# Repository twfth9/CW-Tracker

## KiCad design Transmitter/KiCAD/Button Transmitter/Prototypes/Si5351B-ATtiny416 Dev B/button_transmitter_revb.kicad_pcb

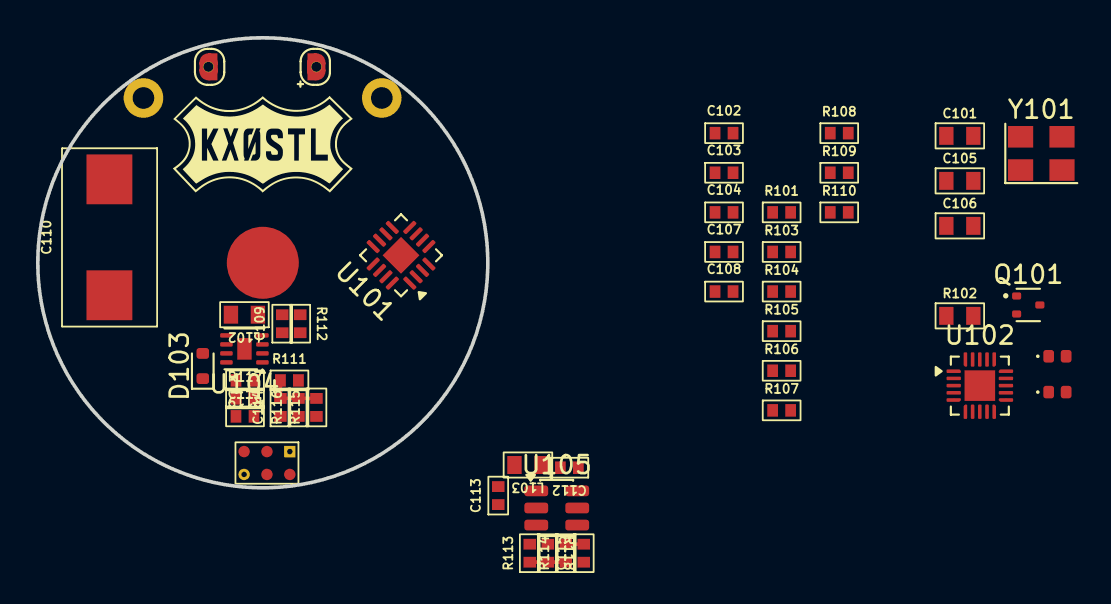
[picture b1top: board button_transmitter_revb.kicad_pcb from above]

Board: 4 copper layers, 25.0 x 25.0 mm, 52 parts (1 on the bottom side), 33 nets.

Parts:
BT101: CR2032; BatteryHolder_Keystone_3034_1x20mm
BZ101: 7BB-20-3; Buzzer_Pad_POS
BZ102: 7BB-20-3; Buzzer_Pad_NEG
C101: 10uF; Worthington_C_0603
C102, C103, C104, C108, C111, C112, C113, C114: 100nF; Worthington_C_0402
C105, C106: 22uF; Worthington_C_0603
C107, C109: 1uF; Worthington_C_0402
C110: 47uF; Worthington_CTant_2917
C115: 220pF; Worthington_C_0402
D101: RED; Worthington_LED_0402_1005Metric
D102: GREEN; Worthington_LED_0402_1005Metric
D103: D_Schottky; D_SOD-523
J101: 1.27mm Pogo Pads For Programming & Debug; 2x3_1.27mm_Pogo_Header
J102: Antenna Spring; RF_Solder_Pad
L101: 100mH; L_Axial_L12.0mm_D5.0mm_P15.24mm_Horizontal_Fastron_MISC
L102: 10uH; Worthington_L_0603
L103: 4u7H; Worthington_L_0603
Q101: DMN601TK-7; SOT-523
R101: 15k; Worthington_R_0402
R102: 15k; Worthington_R_0603
R103: 600; Worthington_R_0402
R104: 0R; Worthington_R_0402
R105, R114, R115: 1k; Worthington_R_0402
R106, R109: 1M; Worthington_R_0402
R107, R108: 10; Worthington_R_0402
R110: 500; Worthington_R_0402
R111: 3M; Worthington_R_0402
R112: 2k2; Worthington_R_0402
R113: 402k; Worthington_R_0402
R116: 200k; Worthington_R_0402
R117: 107k; Worthington_R_0402
R118: 127k; Worthington_R_0402
R119: 5k; Worthington_R_0402
U101: Si5351B-B-GM1; QFN-16-1EP_3x3mm_P0.5mm_EP1.45x1.45mm
U102: ATtiny416-M; VQFN-20-1EP_3x3mm_P0.4mm_EP1.7x1.7mm
U103: Case; Case_CR2032
U104: MIC2288YML; WDFN-8-1EP_2x2mm_P0.5mm_EP0.8x1.2mm
U105: TPP361081; TSOT-23-6
Y101: 25MHz; Crystal_SMD_Kyocera_CX3225SB-4Pin_3.2x2.5mm

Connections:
+2V5: C101.1, C102.1, C103.1, C113.2, D101.2 (A), J101.2, L101.2, L103.2, R101.2, R102.2, R113.2, U101.9 (VDDOA), U101.16 (VDD)
+BATT: C104.1, C105.1, C106.1, U102.4 (VCC)
/2V5_RAIL_EN: U102.5 (PA4), U105.5 (EN)
/BOOST_EN: U102.10 (PB4), U104.3 (EN)
/BUZZER_PULSE: D102.2 (A), R108.1, U102.15 (PC0)
/CHARGE_AIN7: R115.1, U102.8 (PA7)
/CLK3: J102.1 (In), R104.2
/CLK3_T: R104.1, U101.12 (CLK3)
/MCU_DAC0: J101.5, R105.1, U102.7 (PA6)
/MCU_SCL: J101.4, R102.1, U101.4 (SCL), U102.1 (PA2)
/MCU_SDA: J101.3, R101.1, U101.5 (SDA), U102.20 (PA1)
/MCU_UPDI: J101.1, U102.19 (~RESET/PA0)
/~TX_EN: U101.6 (OEB), U102.12 (PB2)
GND: BT101.2, BZ102.2 (-), C101.2, C102.2, C103.2, C104.2, C105.2, C106.2, C108.1, C109.1, C110.2, C111.1, C113.1, C114.1, C115.1, J101.6, Q101.2 (S), R103.2, R106.2, R109.2, R110.2, R116.1, R118.1, R119.1, U101.15 (GND), U101.17 (GND), U102.3 (GND), U102.21 (GND), U104.4 (AGND), U104.8 (PGND), U104.9 (PAD), U105.1 (GND), Y101.2, Y101.4
unnamed: BT101.1 (+), R112.2
unnamed: BZ101.1 (+), C107.2, R106.1
unnamed: C107.1, L101.1, R107.2
unnamed: C114.2, R111.1, R115.2, R116.2
unnamed: D101.1 (K), R103.1
unnamed: D102.1 (K), R110.1
unnamed: D103.2 (A), L102.2, U104.7 (SW)
unnamed: C110.1, C111.2, D103.1 (K), R111.2, R117.2, U104.1 (OVP), U105.3 (VIN)
unnamed: Q101.3 (D), R107.1
unnamed: Q101.1 (G), R108.2, R109.1
unnamed: R113.1, R114.1, R118.2
unnamed: C108.2, R105.2, U101.3 (VC)
unnamed: U101.1 (XA), Y101.3
unnamed: U101.2 (XB), Y101.1
unnamed: R117.1, R119.2, U104.6 (FB)
unnamed: C109.2, L102.1, R112.1, U104.2 (VIN)
unnamed: C112.2, L103.1, U105.2 (SW)
unnamed: C112.1, U105.6 (VBST)
unnamed: C115.2, R114.2, U105.4 (VFB)

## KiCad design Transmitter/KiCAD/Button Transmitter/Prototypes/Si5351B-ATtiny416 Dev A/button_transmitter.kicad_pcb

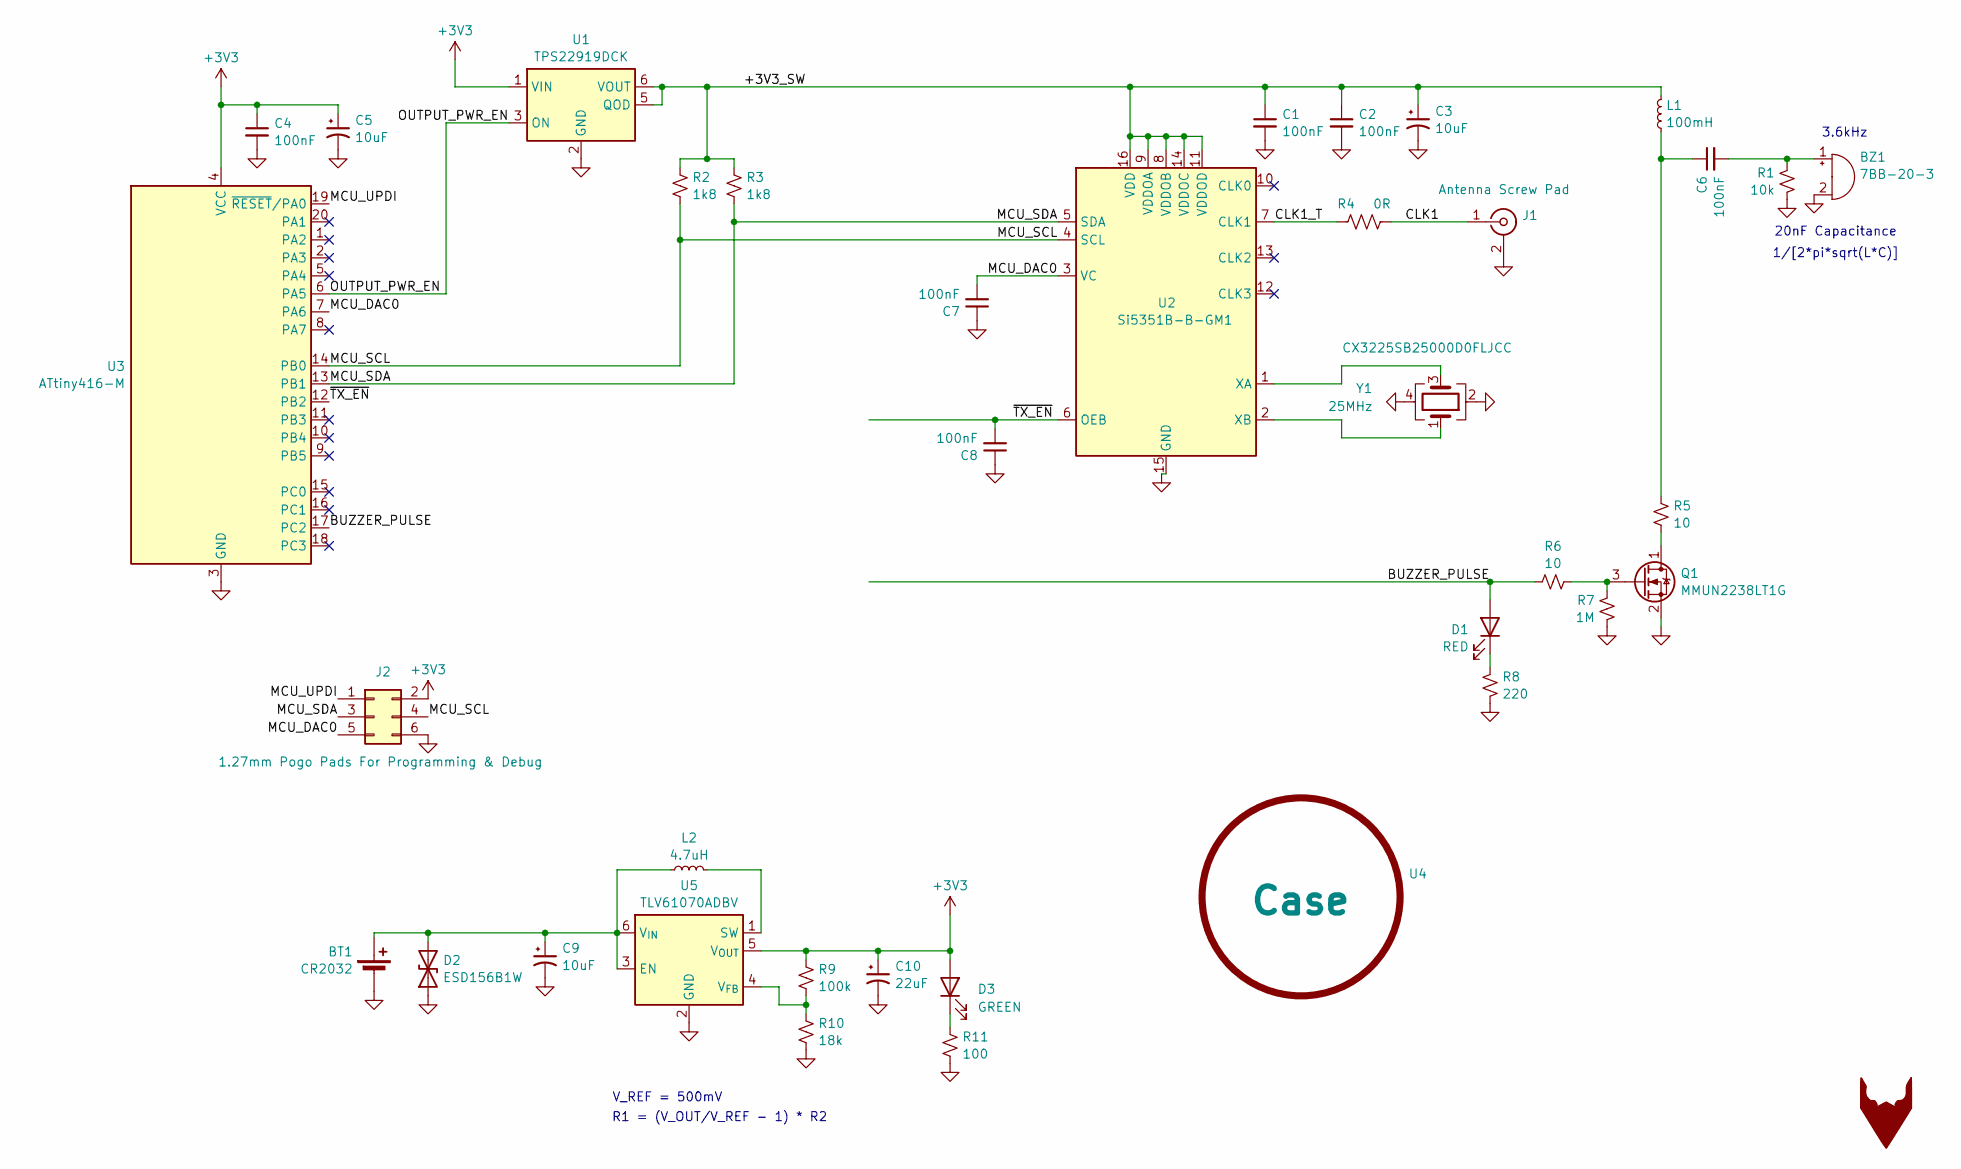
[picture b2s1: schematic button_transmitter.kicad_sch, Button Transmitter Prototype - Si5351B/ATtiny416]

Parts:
BT1: CR2032; BatteryHolder_Keystone_3034_1x20mm_CUTOUT
BZ1: 7BB-20-3; Buzzer_Pad_POS
BZ2-1: 7BB-20-3; Buzzer_Pad_NEG
C1, C2, C4, C6, C7, C8: 100nF; Worthington_C_0402_1005Metric
C3, C5, C9: 10uF; Worthington_C_0402_1005Metric
C10: 22uF; C_0603_1608Metric
D1: RED; Worthington_LED_0402_1005Metric
D2: ESD156B1W; D_0201_0603Metric
D3: GREEN; Worthington_LED_0402_1005Metric
J1: Antenna Screw Pad; RF_Solder_Pad
J2: 1.27mm Pogo Pads For Programming & Debug; 2x3_1.27mm_Pogo_Header
L1: 100mH; L_Axial_L12.0mm_D5.0mm_P15.24mm_Horizontal_Fastron_MISC
L2: 4.7uH; L_0805_2012Metric
Q1: MMUN2238LT1G; SOT-23-3
R1: 10k; Worthington_R_0402_1005Metric
R2: 1k8; R_0402_1005Metric
R3: 1k8; R_0603_1608Metric
R4: 0R; Worthington_R_0402_1005Metric
R5, R6: 10; Worthington_R_0402_1005Metric
R7: 1M; Worthington_R_0402_1005Metric
R8: 220; Worthington_R_0402_1005Metric
R9: 100k; Worthington_R_0402_1005Metric
R10: 18k; Worthington_R_0402_1005Metric
R11: 100; Worthington_R_0402_1005Metric
U1: TPS22919DCK; SOT-363_SC-70-6
U2: Si5351B-B-GM1; QFN-16-1EP_3x3mm_P0.5mm_EP1.45x1.45mm
U3: ATtiny416-M; VQFN-20-1EP_3x3mm_P0.4mm_EP1.7x1.7mm
U4: Case; Case_CR2032
U5: TLV61070ADBV; SOT-23-6
Y1: 25MHz; Crystal_SMD_Kyocera_CX3225SB-4Pin_3.2x2.5mm

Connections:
+3V3: C4.1, C5.1, C10.1, D3.2 (A), J2.2, R9.1, U1.1 (VIN), U3.4 (VCC), U5.5 (V_{OUT})
/+3V3_SW: C1.1, C2.1, C3.1, L1.2, R2.1, R3.1, U1.5 (QOD), U1.6 (VOUT), U2.8 (VDDOB), U2.9 (VDDOA), U2.11 (VDDOD), U2.14 (VDDOC), U2.16 (VDD)
/BUZZER_PULSE: D1.2 (A), R6.1, U3.17 (PC2)
/CLK1: J1.1 (In), R4.2
/CLK1_T: R4.1, U2.7 (CLK1)
/MCU_DAC0: C7.2, J2.5, U2.3 (VC), U3.7 (PA6)
/MCU_SCL: J2.4, R2.2, U2.4 (SCL), U3.14 (PB0)
/MCU_SDA: J2.3, R3.2, U2.5 (SDA), U3.13 (PB1)
/MCU_UPDI: J2.1, U3.19 (~RESET/PA0)
/OUTPUT_PWR_EN: U1.3 (ON), U3.6 (PA5)
/~TX_EN: C8.2, U2.6 (OEB), U3.12 (PB2)
GND: BT1.2, BZ2-1.2 (-), C1.2, C2.2, C3.2, C4.2, C5.2, C7.1, C8.1, C9.2, C10.2, D2.1 (A1), J1.2 (Ext), J2.6, Q1.2 (S), R1.2, R7.2, R8.2, R10.2, R11.2, U1.2 (GND), U2.15 (GND), U2.17 (GND), U3.3 (GND), U3.21 (GND), U5.2 (GND), Y1.2, Y1.4
unnamed: BT1.1 (+), C9.1, D2.2 (A2), L2.1, U5.3 (EN), U5.6 (V_{IN})
unnamed: BZ1.1 (+), C6.2, R1.1
unnamed: C6.1, L1.1, R5.2
unnamed: D1.1 (K), R8.1
unnamed: D3.1 (K), R11.1
unnamed: Q1.1 (D), R5.1
unnamed: Q1.3 (G), R6.2, R7.1
unnamed: U2.1 (XA), Y1.3
unnamed: U2.2 (XB), Y1.1
unnamed: L2.2, U5.1 (SW)
unnamed: R9.2, R10.1, U5.4 (V_{FB})

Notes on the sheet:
20nF Capacitance
3.6kHz
1/[2*pi*sqrt(L*C)]
V_REF = 500mV
R1 = (V_OUT/V_REF - 1) * R2

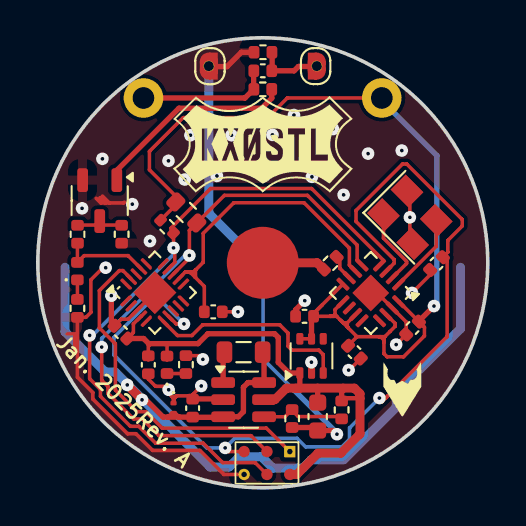
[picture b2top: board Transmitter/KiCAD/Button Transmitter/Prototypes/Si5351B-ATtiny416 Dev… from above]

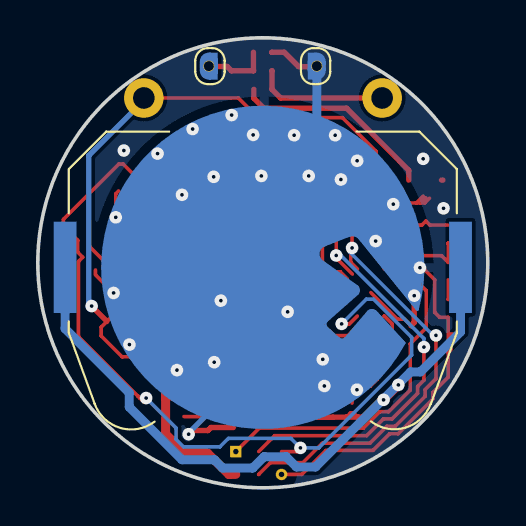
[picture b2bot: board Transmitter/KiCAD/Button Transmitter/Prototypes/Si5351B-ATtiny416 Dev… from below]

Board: 2 copper layers, 25.0 x 25.0 mm, 38 parts (3 on the bottom side), 23 nets.

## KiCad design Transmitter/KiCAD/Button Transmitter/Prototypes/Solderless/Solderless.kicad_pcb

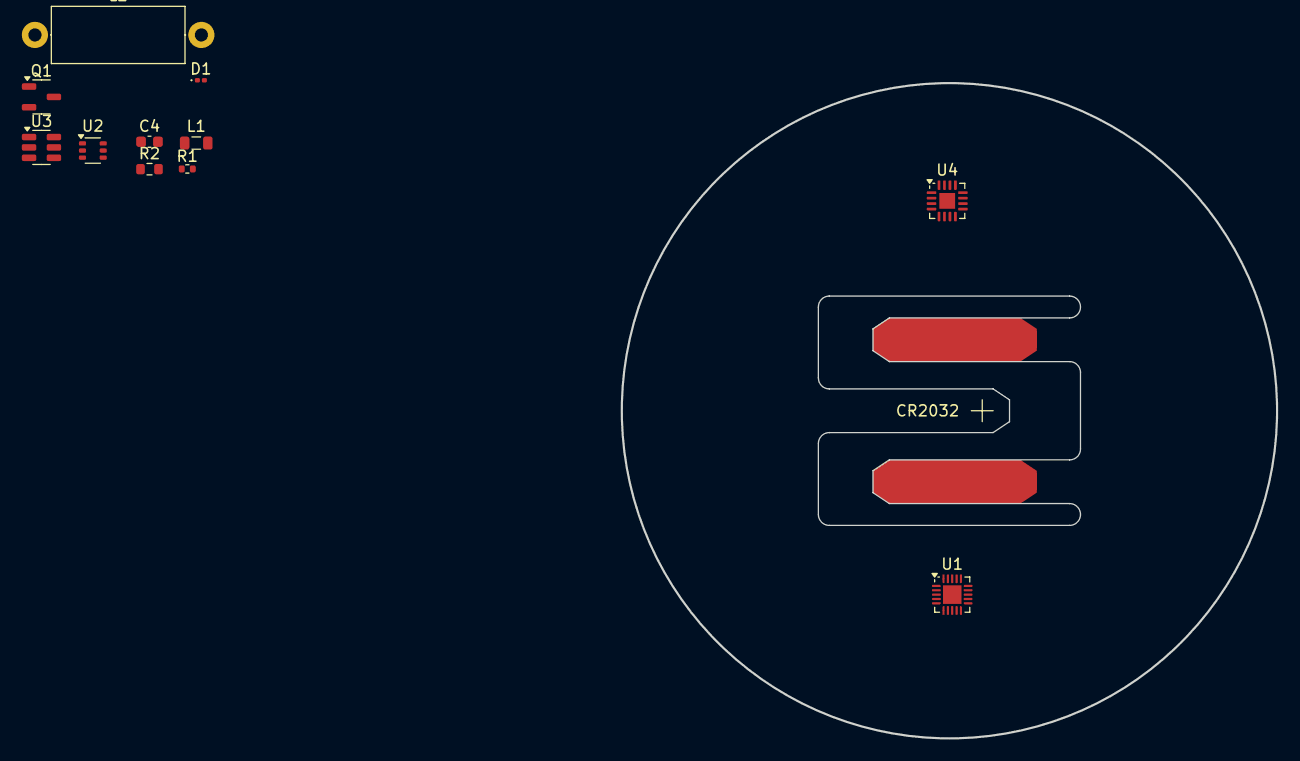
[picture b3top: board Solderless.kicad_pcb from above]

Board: 2 copper layers, 60.0 x 60.0 mm, 12 parts (0 on the bottom side), 10 nets, no tracks yet.

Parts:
BT1: Battery_Cell; CR2032_PCBcutout
C4: 22uF; C_0603_1608Metric
D1: ESD156B1W; D_0201_0603Metric
L1: 4.7uH; L_0805_2012Metric
L2: 100mH; L_Axial_L12.0mm_D5.0mm_P15.24mm_Horizontal_Fastron_MISC
Q1: MMUN2238LT1G; SOT-23-3
R1: 1k8; R_0402_1005Metric
R2: 1k8; R_0603_1608Metric
U1: ATtiny416-M; VQFN-20-1EP_3x3mm_P0.4mm_EP1.7x1.7mm
U2: TPS22919DCK; SOT-363_SC-70-6
U3: TLV61070ADBV; SOT-23-6
U4: Si5351B-B-GM1; QFN-16-1EP_3x3mm_P0.5mm_EP1.45x1.45mm

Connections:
+3V3: C4.1, U1.4 (VCC), U2.1 (VIN), U3.5 (V_{OUT})
/+3V3_SW: L2.2, R1.1, R2.1, U2.5 (QOD), U2.6 (VOUT), U4.8 (VDDOB), U4.9 (VDDOA), U4.11 (VDDOD), U4.14 (VDDOC), U4.16 (VDD)
/MCU_DAC0: U1.7 (PA6), U4.3 (VC)
/MCU_SCL: R1.2, U1.14 (PB0), U4.4 (SCL)
/MCU_SDA: R2.2, U1.13 (PB1), U4.5 (SDA)
/OUTPUT_PWR_EN: U1.6 (PA5), U2.3 (ON)
/~TX_EN: U1.12 (PB2), U4.6 (OEB)
GND: C4.2, D1.1 (A1), Q1.2 (S), U1.3 (GND), U1.21 (GND), U2.2 (GND), U3.2 (GND), U4.15 (GND), U4.17 (GND)
unnamed: D1.2 (A2), L1.1, U3.3 (EN), U3.6 (V_{IN})
unnamed: L1.2, U3.1 (SW)

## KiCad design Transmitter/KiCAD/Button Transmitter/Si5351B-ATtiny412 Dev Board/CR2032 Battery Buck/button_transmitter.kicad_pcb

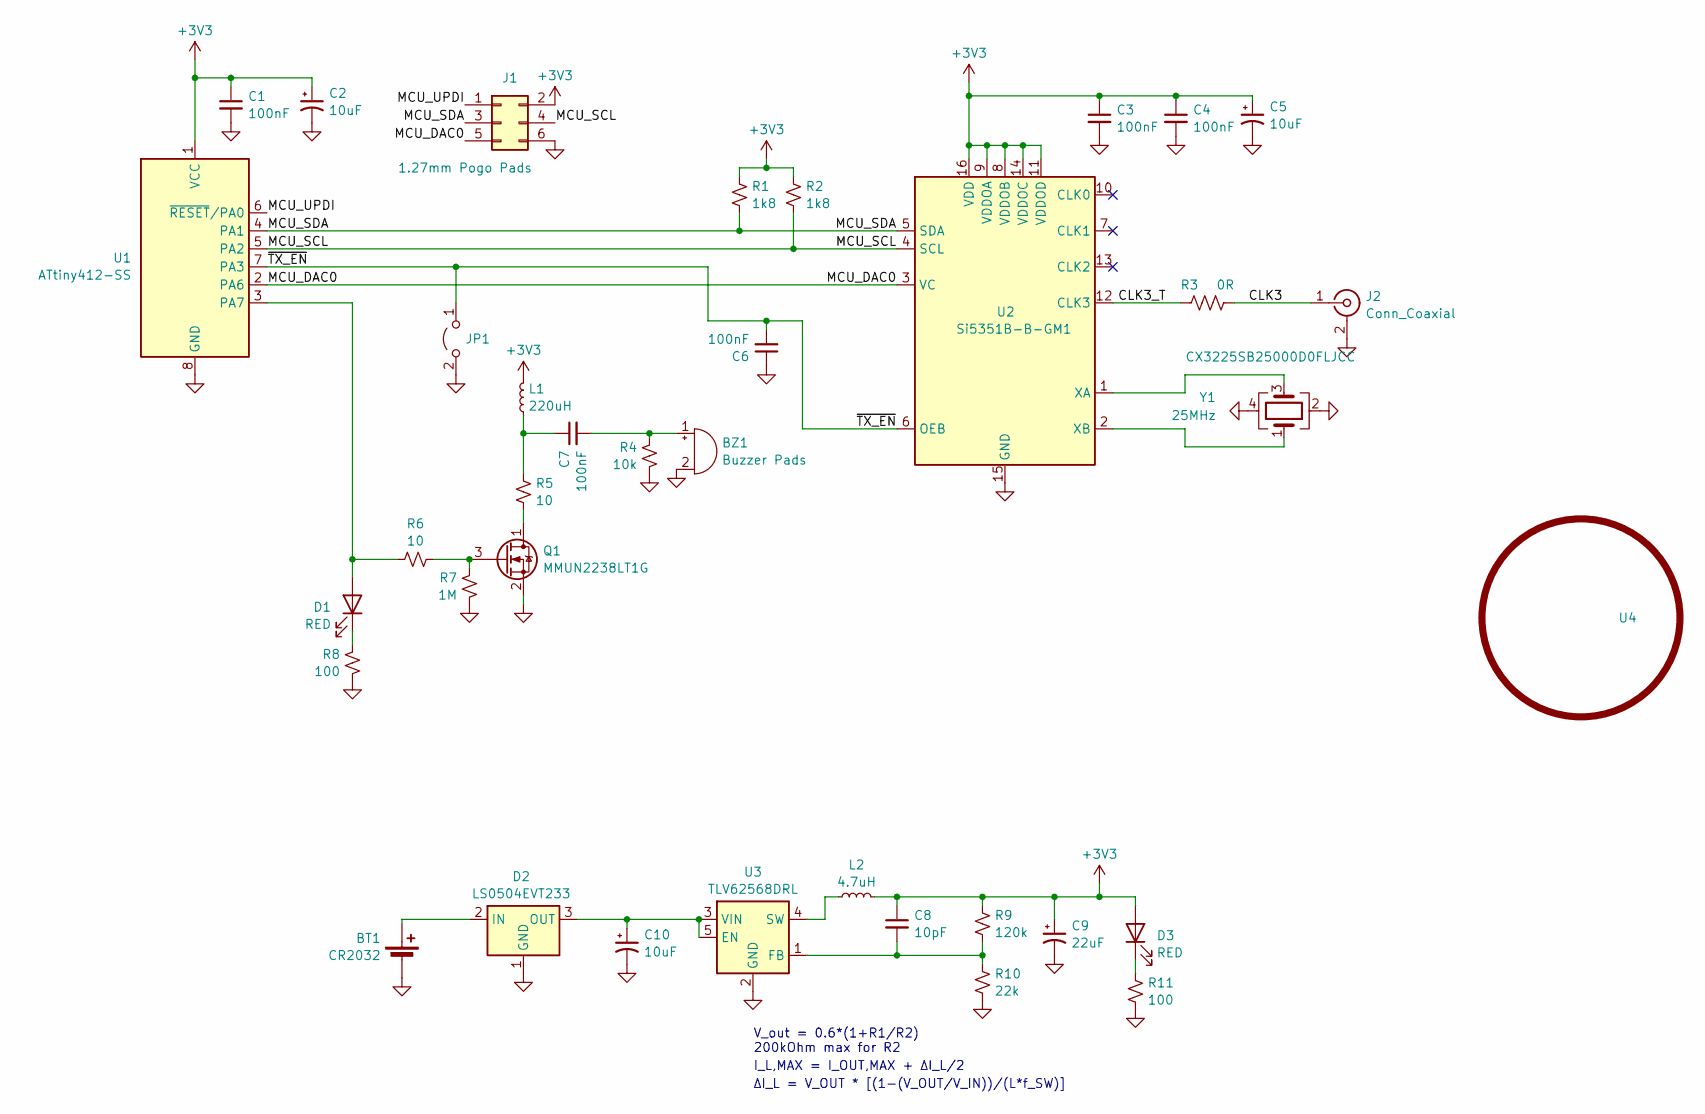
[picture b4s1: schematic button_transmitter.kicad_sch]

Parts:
BT1: CR2032; BatteryHolder_Keystone_3034_1x20mm
BZ1: Buzzer Pads; SolderJumper-2_P1.3mm_Open_RoundedPad1.0x1.5mm
C1, C3, C4, C6, C7: 100nF; R_0402_1005Metric
C2, C5, C10: 10uF; R_0402_1005Metric
C8: 10pF; R_0402_1005Metric
C9: 22uF; R_0603_1608Metric
D1, D3: RED; LED_0402_1005Metric
D2: LS0504EVT233; SOT-23-3
J1: 1.27mm Pogo Pads; 2x3_1.27mm_Pogo_Header
J2: Conn_Coaxial; RF_Solder_Pad
JP1: Jumper_2_Open; SolderJumper-2_P1.3mm_Open_TrianglePad1.0x1.5mm
L1: 220uH; L_1008_2520Metric
L2: 4.7uH; L_0805_2012Metric
Q1: MMUN2238LT1G; SOT-23-3
R1, R2: 1k8; R_0402_1005Metric
R3: 0R; R_0402_1005Metric
R4: 10k; R_0402_1005Metric
R5, R6: 10; R_0402_1005Metric
R7: 1M; R_0402_1005Metric
R8, R11: 100; R_0402_1005Metric
R9: 120k; R_0402_1005Metric
R10: 22k; R_0402_1005Metric
U1: ATtiny412-SS; SOIC-8_3.9x4.9mm_P1.27mm
U2: Si5351B-B-GM1; QFN-16-1EP_3x3mm_P0.5mm_EP1.45x1.45mm
U3: TLV62568DRL; SOT-563
U4: Case_CR2032
Y1: 25MHz; Crystal_SMD_Kyocera_CX3225SB-4Pin_3.2x2.5mm

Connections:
+3V3: C1.1, C2.1, C3.1, C4.1, C5.1, C8.1, C9.1, D3.2 (A), J1.2, L1.2, L2.2, R1.1, R2.1, R9.1, U1.1 (VCC), U2.8 (VDDOB), U2.9 (VDDOA), U2.11 (VDDOD), U2.14 (VDDOC), U2.16 (VDD)
/CLK3: J2.1 (In), R3.2
/CLK3_T: R3.1, U2.12 (CLK3)
/MCU_DAC0: J1.5, U1.2 (PA6), U2.3 (VC)
/MCU_SCL: J1.4, R2.2, U1.5 (PA2), U2.4 (SCL)
/MCU_SDA: J1.3, R1.2, U1.4 (PA1), U2.5 (SDA)
/MCU_UPDI: J1.1, U1.6 (~RESET/PA0)
/~TX_EN: C6.2, JP1.1 (A), U1.7 (PA3), U2.6 (OEB)
GND: BT1.2 (-), BZ1.2 (-), C1.2, C2.2, C3.2, C4.2, C5.2, C6.1, C9.2, C10.2, D2.1 (GND), J1.6, J2.2 (Ext), JP1.2 (B), Q1.2 (S), R4.2, R7.2, R8.2, R10.2, R11.2, U1.8 (GND), U2.15 (GND), U3.2 (GND), Y1.2, Y1.4
unnamed: BT1.1 (+), D2.2 (IN)
unnamed: BZ1.1 (+), C7.2, R4.1
unnamed: C7.1, L1.1, R5.2
unnamed: D1.2 (A), R6.1, U1.3 (PA7)
unnamed: D1.1 (K), R8.1
unnamed: C10.1, D2.3 (OUT), U3.3 (VIN), U3.5 (EN)
unnamed: D3.1 (K), R11.1
unnamed: Q1.1 (D), R5.1
unnamed: Q1.3 (G), R6.2, R7.1
unnamed: U2.1 (XA), Y1.3
unnamed: U2.2 (XB), Y1.1
unnamed: C8.2, R9.2, R10.1, U3.1 (FB)
unnamed: L2.1, U3.4 (SW)

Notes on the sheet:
V_out = 0.6*(1+R1/R2) 200kOhm max for R2
ΔI_L = V_OUT * [(1-(V_OUT/V_IN))/(L*f_SW)]
I_L,MAX = I_OUT,MAX + ΔI_L/2

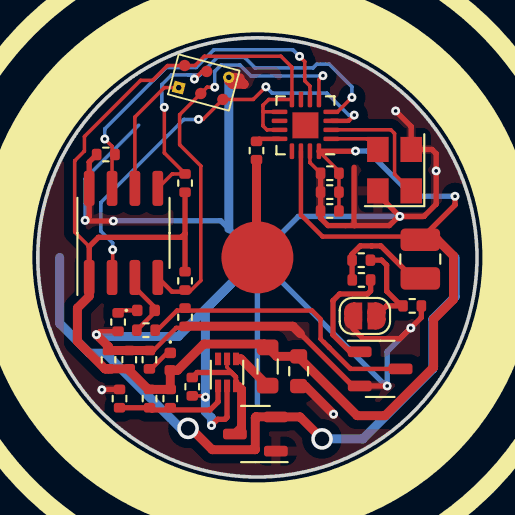
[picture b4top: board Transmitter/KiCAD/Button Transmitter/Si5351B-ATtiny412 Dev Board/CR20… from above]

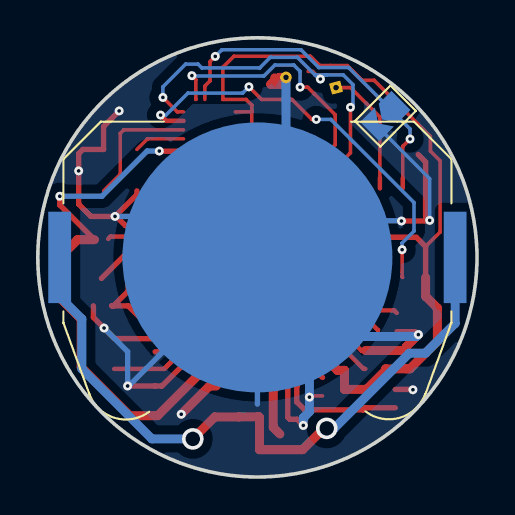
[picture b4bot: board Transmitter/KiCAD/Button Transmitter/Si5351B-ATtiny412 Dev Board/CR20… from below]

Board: 2 copper layers, 24.4 x 24.4 mm, 37 parts (2 on the bottom side), 22 nets.

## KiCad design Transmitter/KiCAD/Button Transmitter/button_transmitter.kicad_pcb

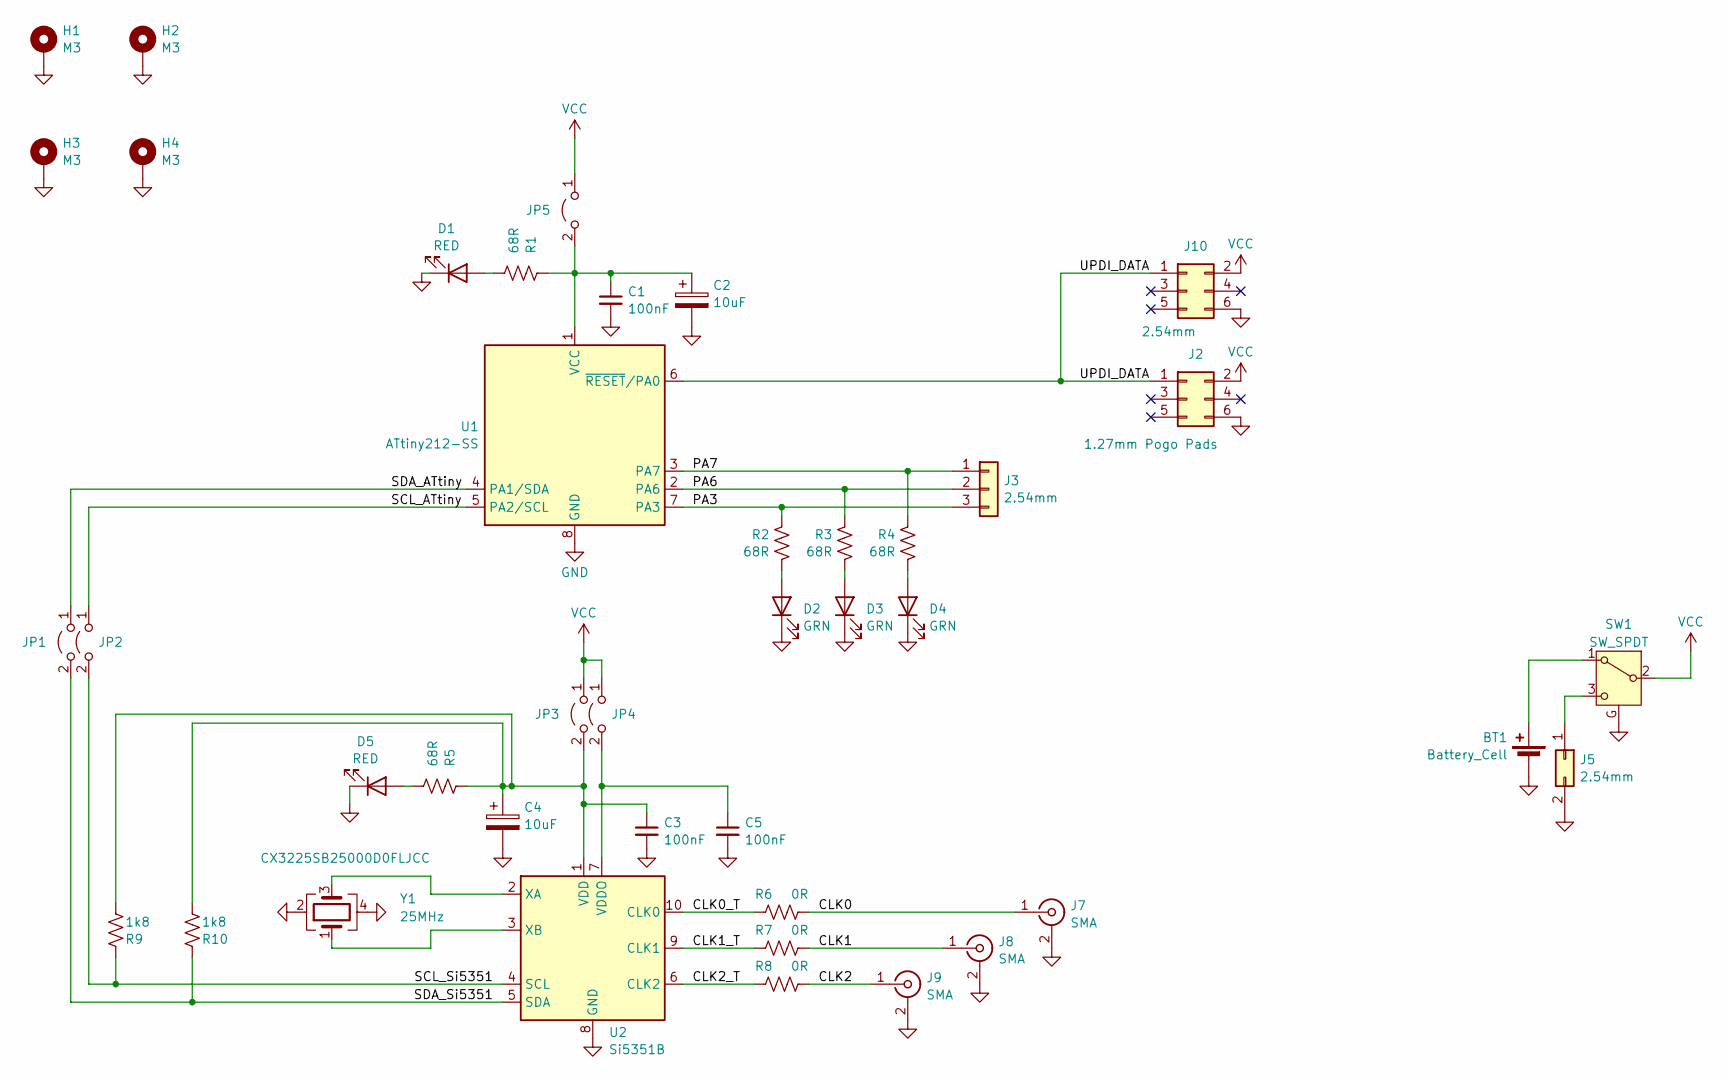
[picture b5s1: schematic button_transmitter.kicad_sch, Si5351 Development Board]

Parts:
BT1: Battery_Cell; BAT_1066
C1, C3, C5: 100nF; C_0603_1608Metric_Pad1.08x0.95mm_HandSolder
C2, C4: 10uF; C_0805_2012Metric_Pad1.18x1.45mm_HandSolder
D1, D5: RED; LED_0603_1608Metric_Pad1.05x0.95mm_HandSolder
D2, D3, D4: GRN; LED_0603_1608Metric_Pad1.05x0.95mm_HandSolder
H1, H2, H3, H4: M3; MountingHole_3.2mm_M3_Pad
J2: 1.27mm Pogo Pads; 2x3_1.27mm_Pogo_Header
J3: 2.54mm; PinHeader_1x03_P2.54mm_Vertical
J5: 2.54mm; PinHeader_1x02_P2.54mm_Vertical
J7, J8, J9: SMA; SMA_Amphenol_132134-16_Vertical
J10: 2.54mm; PinHeader_2x03_P2.54mm_Vertical
JP1, JP2, JP3, JP4, JP5: Jumper_2_Open; SolderJumper-2_P1.3mm_Open_TrianglePad1.0x1.5mm
R1, R2, R3, R4, R5: 68R; R_0603_1608Metric_Pad0.98x0.95mm_HandSolder
R6, R7, R8: 0R; R_0603_1608Metric_Pad0.98x0.95mm_HandSolder
R9, R10: 1k8; R_1206_3216Metric
SW1: SW_SPDT; SLW-121586-5A-D
U1: ATtiny212-SS; SOIC-8_3.9x4.9mm_P1.27mm
U2: Si5351B; MSOP-10_3x3mm_P0.5mm
Y1: 25MHz; Crystal_SMD_Kyocera_CX3225SB-4Pin_3.2x2.5mm

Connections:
/CLK0: J7.1 (In), R6.2
/CLK0_T: R6.1, U2.10 (CLK0)
/CLK1: J8.1 (In), R7.2
/CLK1_T: R7.1, U2.9 (CLK1)
/CLK2: J9.1 (In), R8.2
/CLK2_T: R8.1, U2.6 (CLK2)
/PA3: J3.3, R2.1, U1.7 (PA3)
/PA6: J3.2, R3.1, U1.2 (PA6)
/PA7: J3.1, R4.1, U1.3 (PA7)
/SCL_ATtiny: JP2.1 (A), U1.5 (PA2/SCL)
/SCL_Si5351: JP2.2 (B), R9.1, U2.4 (SCL)
/SDA_ATtiny: JP1.1 (A), U1.4 (PA1/SDA)
/SDA_Si5351: JP1.2 (B), R10.1, U2.5 (SDA)
/UPDI_DATA: J2.1, J10.1, U1.6 (~RESET/PA0)
GND: BT1.N (-), C1.2, C2.2, C3.2, C4.2, C5.2, D1.1 (K), D2.1 (K), D3.1 (K), D4.1 (K), D5.1 (K), H1.1, H2.1, H3.1, H4.1, J2.6, J5.2, J7.2 (Ext), J8.2 (Ext), J9.2 (Ext), J10.6, SW1.G, U1.8 (GND), U2.8 (GND), Y1.2, Y1.4
unnamed: BT1.P (+), SW1.1 (A)
unnamed: D1.2 (A), R1.2
unnamed: D2.2 (A), R2.2
unnamed: D3.2 (A), R3.2
unnamed: D4.2 (A), R4.2
unnamed: D5.2 (A), R5.2
unnamed: J5.1, SW1.3 (C)
unnamed: C3.1, C4.1, JP3.2 (B), R5.1, R9.2, R10.2, U2.1 (VDD)
unnamed: C5.1, JP4.2 (B), U2.7 (VDDO)
unnamed: C1.1, C2.1, JP5.2 (B), R1.1, U1.1 (VCC)
unnamed: U2.2 (XA), Y1.3
unnamed: U2.3 (XB), Y1.1
VCC: J2.2, J10.2, JP3.1 (A), JP4.1 (A), JP5.1 (A), SW1.2 (B)

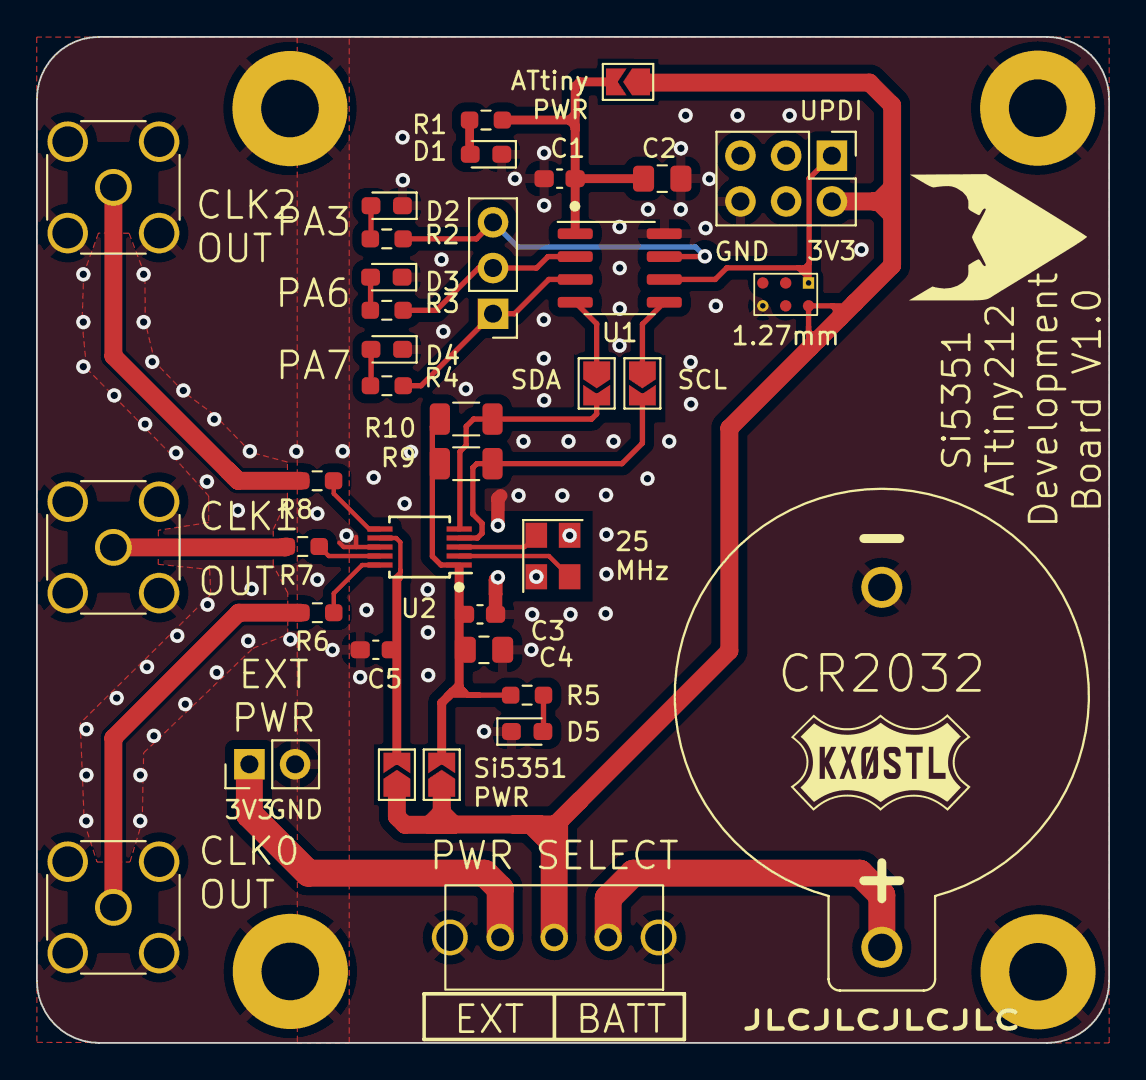
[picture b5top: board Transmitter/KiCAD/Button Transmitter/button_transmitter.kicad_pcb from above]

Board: 2 copper layers, 59.6 x 55.9 mm, 41 parts (0 on the bottom side), 28 nets.

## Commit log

2024-07-17 Created Development Board v1.0 files
2024-07-17 Generated gerber files for V1.0 of dev board
2024-07-17 Added JLC order number to gerber files
2024-07-17 Changed board to purple
2024-08-06 Things
2024-12-31 Created PCB 3D model for 330mAh transmitter version
2024-12-31 Created directory for CR2032 version
2025-01-01 Pause point in CR2032 layout
2025-01-01 Finished CR2032 layout
    I realize now that I should replace the buck converter with a boost converter, going to make a modified version that uses that instead
2025-01-03 Completed pcb of CR2032 layout
    I realize now that I put the pads for the buzzer on the wrong side of the board, so I need to redo a large part of it. womp womp
2025-01-04 Finished CR2032 PCB layout
    I like this. This is good
2025-01-05 Added logos to silkscreen
2025-01-05 Generated gerbers, added Morgan's 3D models
2025-01-09 Remade gerber files, sent to JLCPCB
2025-01-22 Removed files where the names were too long
2025-01-23 Corrected BOM
2025-09-18 First working prototype of Si5351B transmitter using dev board
2025-09-20 First drafts of Si5351B software on button rev A
2025-09-29 Starting ATtiny412 Dev B
2025-09-29 Schematic edits, supercap?
2025-10-14 Rev B design work
2025-10-18 Dev 2 Schematic work
2025-10-18 More Dev B schematic tweaks
2025-10-27 Beginnings of low power boost converter design
